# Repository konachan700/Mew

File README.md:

## Mew - hardware password manager

*   [Forum](https://forum.mewhpm.com)
*   [Wiki](https://wiki.mewhpm.com)
*   [Code repo (github)](https://github.com/konachan700/Mew)
*   [Code repo (gitlab mirror)](https://gitlab.com/mewhpm/Mew)
*   [Hardware](https://easyeda.com/konachan.700/MeW_Pro_v2.1)
*	[Android app sources](https://github.com/konachan700/Mew/tree/master/software/MeWSync)

##### • What is it?
It's a small USB device to hold your passwords, private keys and cryptowallets.

*   Easy to use.
*   Fully open sourced.
*   No drivers or propietary software required.
*   Highly protected for critical data.

##### • How does it work?

Connect MeW to a PC or mobile device. Pair MeW with your smartphone via bluetooth. Install the MeW HPM app from Google Play or Appstore. Use it.  

_Demo video will be here a bit later :3_

12 passwords, those you use more often, can be entered directly on the device. Other passwords could be entered by MeW HPM app.  

_Demo video will be here a bit later :3_

You can exchange public keys with your friends directly via bluetooth.

Technically, it is a HID-keyboard.

Passwords are not stored in the device, all passwords are generated on-the-fly depending on the entered PIN-code and internal master key. Nobody and nothing can steal your passwords database, because there is none. If anybody steals the device, he can't bruteforce it - for each PIN-code the device generate different passwords, and, if you set this option, fake logins will be shown.  

Your private keys and wallets, that are stored on the device, are encrypted with AES-256. Encryption key is generated from master key and pin-code on-the-fly. Master key has been stored internally and can't be extracted, of course, if you set the maximum security level.

##### • I lost my MeW. How can I get my passwords back?

When you are starting your MeW for the first time with normal security level, the device key will shown. Save the device key at a secure place. MeW has a cloud backup for encrypted master keys. For recovery of your passwords on a new device you have to enter a device key in the application, and enter you PIN-code in MeW.

In the high security mode cloud backup will disabled, because in this mode the encrypted master key i can't be extracted from the device. If you lose your MeW or forgot a PIN-code, you loose all you passwords.

## • Android application screenshots
&nbsp;&nbsp;&nbsp;&nbsp;&nbsp;&nbsp;&nbsp;&nbsp;&nbsp;&nbsp;&nbsp;&nbsp;

## • Device photos
&nbsp;&nbsp;&nbsp;&nbsp;

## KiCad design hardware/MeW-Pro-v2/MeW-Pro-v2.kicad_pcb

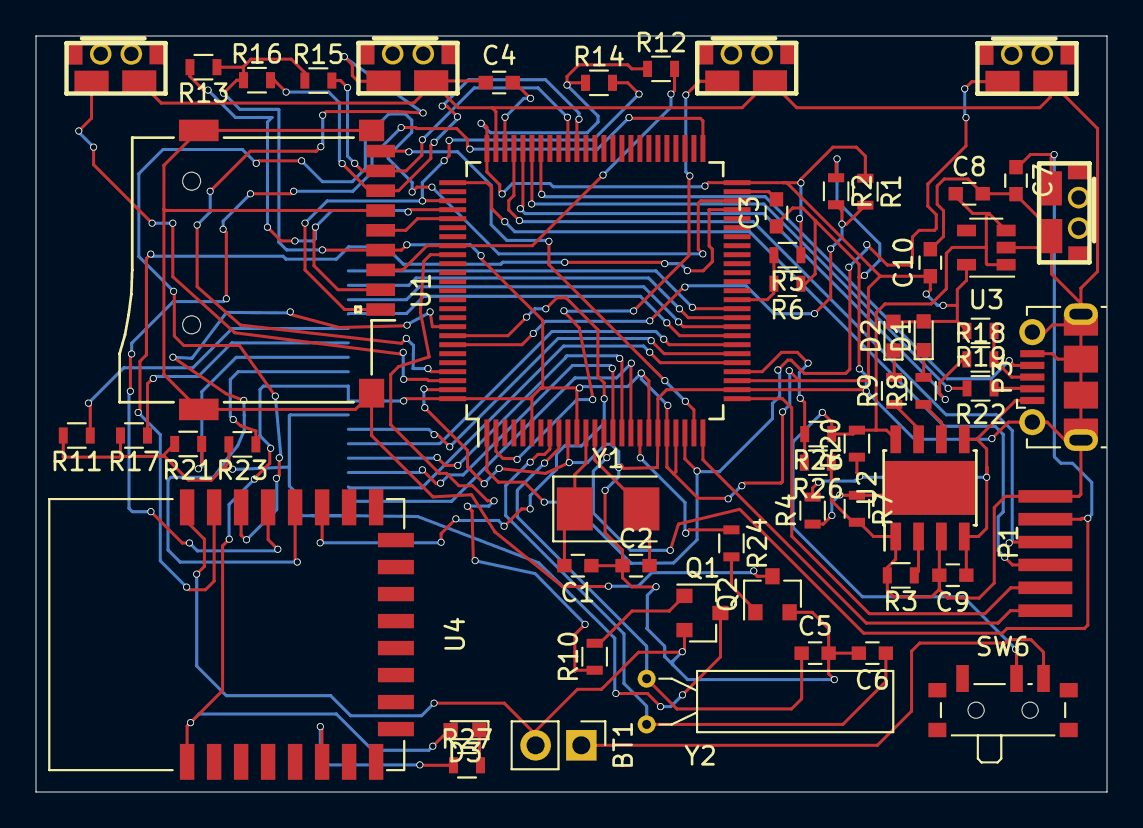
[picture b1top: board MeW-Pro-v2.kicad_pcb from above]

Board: 2 copper layers, 59.5 x 42.0 mm, 59 parts (1 on the bottom side), 68 nets.

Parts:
BT1: Battery; Pin_Header_Straight_1x02_Pitch2.54mm
C1, C2, C5, C6: 22; C_0603
C3, C4: 2.2uF; C_0603
C7: 0.1uF; C_0603
C8, C9, C10: 1uF; C_0603
CON1: uSD_Card; Conn_uSDcard
D1, D2, D3: LED; LED_0603
P1: CONN_01X06; debug_conn_x6
P2: CONN_01X18; DISP1
P3: USB_OTG; USB_Micro-B_Molex-105017-0001
Q1, Q2: 2N7002; SOT-23
R1, R2, R4, R5, R6, R7, R20: 0; R_0603
R3: 10k; R_0603
R8, R9, R19, R27: 1k5; R_0603
R10, R24: 100; R_0603
R11, R17, R21, R23: 63; R_0603
R12, R13, R14, R15, R16: 33k; R_0603
R18, R22: 22R; R_0603
R25, R26: 100k; R_0603
SW1: SW_UP; SMDBTN2
SW2: SW_DOWN; SMDBTN2
SW3: SW_OK; SMDBTN2
SW4: SW_BACK; SMDBTN2
SW5: SW_RESET; SMDBTN2
SW6: SWITCH_INV; SW_SPDT_PCM12
U1: STM32F437VGTx; LQFP-100_14x14mm_Pitch0.5mm
U2: TP4056; SOIC-8_3.9x4.9mm_Pitch1.27mm_9pin
U3: TLV70230DBV; SOT-23-5
U4: JDY-08; JDY-08_HandSoldering
Y1: Crystal; Crystal_SMD_5032-2pin_5.0x3.2mm
Y2: Crystal; Crystal_AT310_d3.0mm_l10.0mm_Horizontal

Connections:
+3V3: C10.1, CON1.4, D1.2, D2.2, D3.2, P2.9, P2.10, R1.1, R5.1, R12.1, R13.1, R14.1, R15.1, R16.1, R19.2, U1.6, U1.11, U1.19, U1.21, U1.22, U1.28, U1.50, U1.75, U1.100, U3.5, U4.1
/5v-usb: C9.1, P3.1, R4.2, R20.1, U2.4, U2.5
/BLE-IO-OFF: U1.51, U4.21
/BLE-PWRC: U1.48, U4.22
/BLE-RESET: U1.47, U4.23
/BLE-RX: U1.92, U4.20
/BLE-TX: U1.93, U4.19
/BMON: C8.1, R20.2, R25.1, SW6.2, U2.8, U3.1, U3.3
/BOOT0: R1.2, R2.2, U1.94
/BOOT1: R5.2, R6.2, U1.37
/CARD_GND: CON1.6, Q2.3
/CARD_PWR: R24.1, U1.18
/DISP_CLK: P2.3, U1.30
/DISP_CS: P2.5, U1.16
/DISP_D/C: P2.4, U1.15
/DISP_MISO: P2.7, U1.31
/DISP_MOSI: P2.6, U1.32
/DISP_PWR: R10.1, U1.84
/DISP_RES: P2.2, U1.17
/LED-B1: R8.1, U2.6
/LED-B2: R9.1, U2.7
/RESET: C7.1, P1.5, SW5.1, U1.14
/SDIO-CD: CON1.9, U1.24
/SDIO-CLK: CON1.5, U1.80
/SDIO-CMD: CON1.3, R12.2, U1.83
/SDIO-D0: CON1.7, R16.2, U1.65
/SDIO-D1: CON1.8, R15.2, U1.66
/SDIO-D2: CON1.1, R14.2, U1.78
/SDIO-D3: CON1.2, R13.2, U1.79
/TOUCH-0: P2.15, U1.33
/TOUCH-1: P2.16, U1.34
/TOUCH-2: P2.17, U1.35
/TOUCH-3: P2.18, U1.36
/USB-DM: R22.2, U1.70
/USB-DP: R18.1, U1.71
/USB-ID: P3.4, U1.69
/WKUP: SW3.1, U1.1, U1.23
/dSWDCLK: P1.3, U1.76
/dSWDIO: P1.4, U1.72
/dUSART-rx: P1.2, U1.26
/dUSART-tx: P1.1, U1.25
GND: BT1.2, C1.1, C2.1, C3.1, C4.1, C5.2, C6.2, C7.2, C8.2, C9.2, C10.2, P1.6, P3.5, P3.6, Q1.2, Q2.2, R2.1, R3.2, R6.1, R7.2, R26.1, SW1.2, SW2.2, SW3.2, SW4.2, SW5.2, U1.10, U1.20, U1.27, U1.74, U1.99, U2.1, U2.3, U3.2, U4.24
unnamed: BT1.1, SW6.3
unnamed: C1.2, U1.12, Y1.1
unnamed: C2.2, U1.13, Y1.2
unnamed: C3.2, U1.49
unnamed: C4.2, U1.73
unnamed: C5.1, U1.9, Y2.2
unnamed: C6.1, U1.8, Y2.1
unnamed: D1.1, R8.2
unnamed: D2.1, R9.2
unnamed: D3.1, R27.2
unnamed: P2.1, P2.8, Q1.3, R11.2, R17.2, R21.2, R23.2
unnamed: P2.11, R23.1
unnamed: P2.12, R21.1
unnamed: P2.13, R17.1
unnamed: P2.14, R11.1
unnamed: P3.2, R22.1
unnamed: P3.3, R18.2, R19.1
unnamed: Q1.1, R10.2
unnamed: Q2.1, R24.2
unnamed: R3.1, U2.2
unnamed: R4.1, R7.1, U2.9
unnamed: R25.2, R26.2, U1.29
unnamed: R27.1, U4.6
unnamed: SW1.1, U1.97
unnamed: SW2.1, U1.98
unnamed: SW4.1, U1.2

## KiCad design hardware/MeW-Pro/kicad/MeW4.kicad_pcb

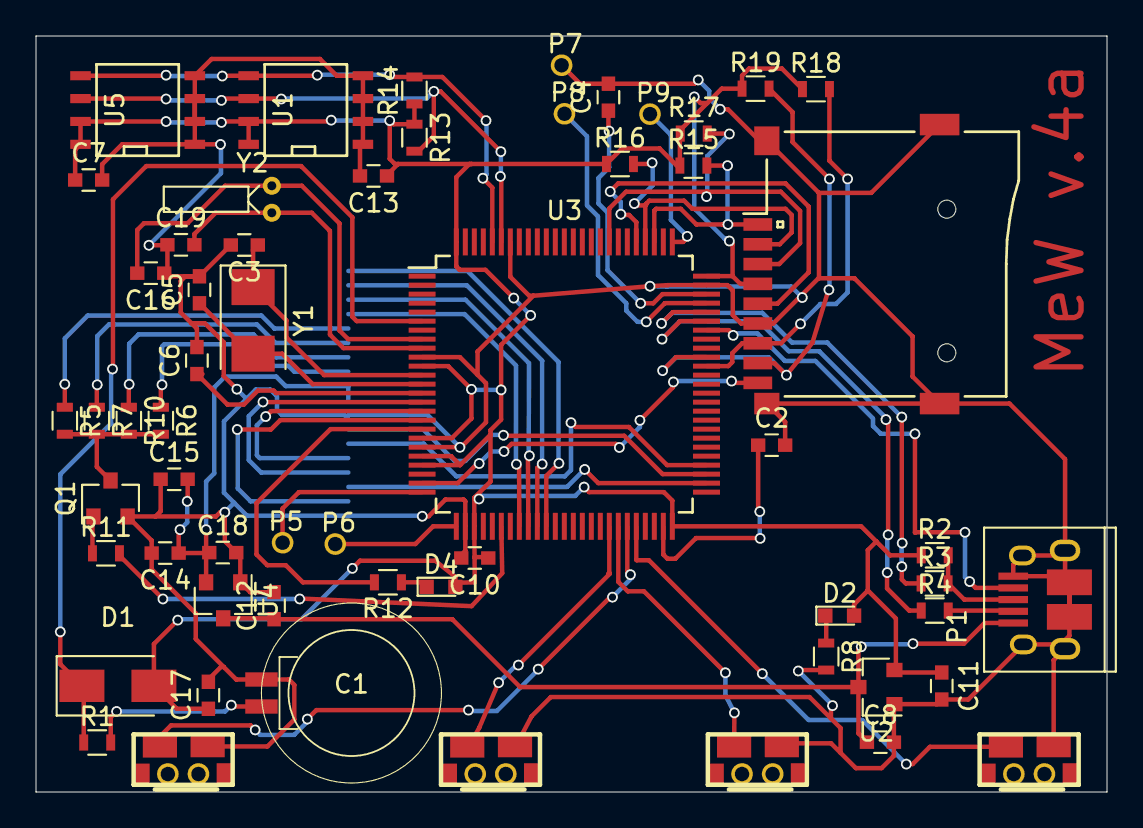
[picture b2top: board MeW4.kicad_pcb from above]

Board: 2 copper layers, 59.5 x 42.0 mm, 59 parts (1 on the bottom side), 55 nets.

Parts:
C1: 0.22F; SCAP-022F
C2, C4: 2.2uF; C_0603
C3, C5, C16, C19: 22; C_0603
C6, C14: 0.1uF; C_0603
C7, C10, C13: 100nF; C_0603
C8, C11, C12, C18: 1uF; C_0603
C15, C17: 0.01uF; C_0603
CON1: uSD_Card; Conn_uSDcard
D1: 1n5819; D_SMA_Standard
D2, D4: LED; LED_0603
P1: USB_OTG; USB_Micro-B_ali1
P4: CONN_01X18; DISP1
P5: TX2; TP_1pin
P6: RX2; TP_1pin
P7: GND; TP_1pin
P8: SWDIO; TP_1pin
P9: SWDCLK; TP_1pin
Q1: 2N7002; SOT-23
R1, R5, R6, R7, R10, R11: 100; R_0603
R2: 1.5k; R_0603
R3, R4: 22; R_0603
R8, R12: 1k; R_0603
R13, R14: 1k5; R_0603
R15, R16, R17, R18, R19: 33k; R_0603
SW1: BACK; SMDBTN2
SW2: ENTER; SMDBTN2
SW3: UP; SMDBTN2
SW4: DOWN; SMDBTN2
U1, U5: 24C16; SOIC-8-N
U2, U4: XC6206P332MR; SOT-23
U3: STM32F217VETx; LQFP-100_14x14mm_Pitch0.5mm
Y1: 8MHz; Crystal_SMD_5032-2pin_5.0x3.2mm
Y2: 32k; Crystal_DS10_d1.0mm_l4.3mm_Horizontal

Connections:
+3V3: C7.1, C10.1, C11.1, C13.1, C17.1, CON1.4, D1.2, D2.2, D4.2, R2.1, R13.1, R14.1, R15.1, R16.1, R17.1, R18.1, R19.1, U1.7, U1.8, U2.2, U3.11, U3.19, U3.21, U3.22, U3.28, U3.50, U3.75, U3.100, U5.7, U5.8
/ADC_1: P4.17, U3.35
/ADC_2: P4.18, U3.36
/B1: SW1.2, U3.43
/B2: SW2.2, U3.44
/B3: SW3.2, U3.45
/B4: SW4.2, U3.46
/CD: CON1.9, U3.24
/DISP_CLK: P4.3, U3.52
/DISP_CS: P4.5, U3.16
/DISP_D/C: P4.4, U3.15
/DISP_MISO: P4.7, U3.53
/DISP_MOSI: P4.6, U3.54
/DISP_PWM: Q1.1, R11.1
/DISP_RES: P4.2, U3.17
/GPIO_X: P4.15, U3.33
/GPIO_Y: P4.16, U3.34
/SDIO_CLK: CON1.5, U3.80
/SDIO_CMD: CON1.3, R17.2, U3.83
/SDIO_D0: CON1.7, R18.2, U3.65
/SDIO_D1: CON1.8, R19.2, U3.66
/SDIO_D2: CON1.1, R15.2, U3.78
/SDIO_D3: CON1.2, R16.2, U3.79
/USB-DM: R4.1, U3.70
/USB-DP: R3.1, U3.71
/USB-ID: P1.4, U3.69
/VBAT_RTC: D1.1, R1.1, U3.6
/i2c_SCL: R13.2, U1.6, U3.95, U5.6
/i2c_SDA: R14.2, U1.5, U3.96, U5.5
GND: C1.2, C2.2, C3.2, C4.2, C5.2, C6.2, C7.2, C8.2, C10.2, C11.2, C12.2, C13.2, C14.2, C15.1, C16.1, C17.2, C18.2, C19.1, CON1.6, P1.5, P1.6, P4.1, P4.8, P7.1, Q1.2, R8.2, SW1.1, SW2.1, SW3.1, SW4.1, U1.1, U1.2, U1.3, U1.4, U2.1, U3.10, U3.20, U3.27, U3.74, U3.94, U4.1, U5.1, U5.2, U5.3, U5.4
unnamed: C1.1, R1.2
unnamed: C2.1, U3.49
unnamed: C3.1, U3.12, Y1.1
unnamed: C4.1, U3.73
unnamed: C5.1, U3.13, Y1.2
unnamed: C6.1, U3.14
unnamed: C8.1, C12.1, P1.1, U2.3, U4.3
unnamed: C14.1, C15.2, C18.1, P4.9, P4.10, U4.2
unnamed: C16.2, U3.8, Y2.1
unnamed: C19.2, U3.9, Y2.2
unnamed: D2.1, R8.1
unnamed: D4.1, R12.1
unnamed: P1.2, R4.2
unnamed: P1.3, R2.2, R3.2
unnamed: P4.11, R6.1
unnamed: P4.12, R10.1
unnamed: P4.13, R7.1
unnamed: P4.14, R5.1
unnamed: P5.1, U3.25
unnamed: P6.1, U3.26
unnamed: P8.1, U3.72
unnamed: P9.1, U3.76
unnamed: Q1.3, R5.2, R6.2, R7.2, R10.2
unnamed: R11.2, U3.31
unnamed: R12.2, U3.18

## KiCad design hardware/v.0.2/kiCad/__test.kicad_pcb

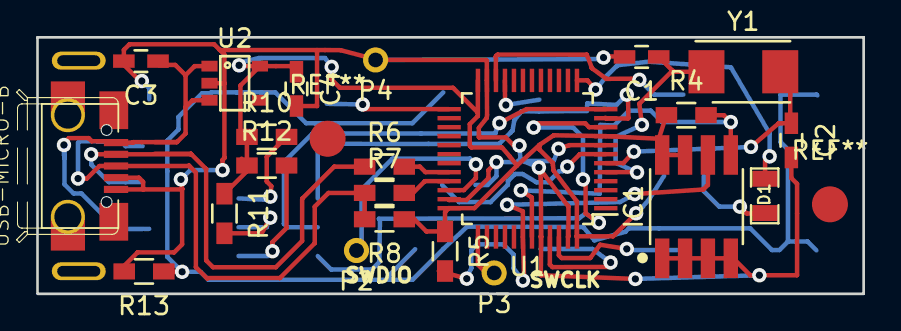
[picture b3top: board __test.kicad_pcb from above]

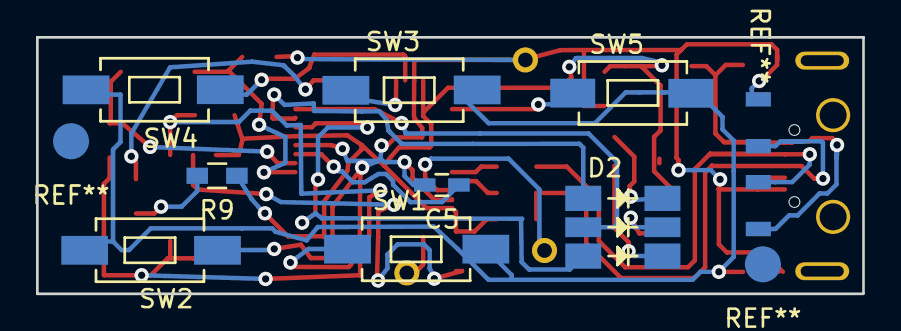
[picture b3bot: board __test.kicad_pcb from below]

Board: 2 copper layers, 45.9 x 14.2 mm, 30 parts (8 on the bottom side), 28 nets.

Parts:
C1, C2: 22; C_0603_HandSoldering
C3: 100nf; C_0603_HandSoldering
C4: 1mf; C_0603_HandSoldering
C5: 0.1mf; C_0603_HandSoldering
CON1: USB-MICRO-B; USB_MICRO_B_SMD
D1: YELLOW; SM0805
D2: LED_RGB_0505; LED_5050_RGB
IC1: ATSHA204A; SO-8_EP1
P2: 1; CONN_2.54mm_1x1
P3: 3; CONN_2.54mm_1x1
P4: 2; CONN_2.54mm_1x1
R4, R5: 1k2; R_0603_HandSoldering
R6, R7: 22; R_0603_HandSoldering
R8, R10, R11, R12: 1k5; R_0603_HandSoldering
R9: 1k; R_0603_HandSoldering
R13: 330; R_0603_HandSoldering
SW1, SW2, SW3, SW4, SW5: SW_PUSH; SW_SPST_EVQPE1
U1: STM32F103C8; LQFP-48_7x7mm_Pitch0.5mm
U2: TLV70033DDC; SOT-23-5
Y1: Crystal; Crystal_SMD_5032_2Pads

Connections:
+3V3: C4.1, IC1.8, R4.1, R5.1, R8.1, R9.1, R10.1, R11.1, R12.1, U1.9, U1.24, U1.36, U1.48, U2.5
/BTN_1: SW1.1, U1.45
/BTN_2: SW2.1, U1.46
/BTN_3: SW3.1, U1.21
/BTN_4: SW4.1, U1.22
/BTN_5: SW5.1, U1.25
/I2C_SCL_1: IC1.6, R5.2, U1.42
/I2C_SDA_1: IC1.5, R4.2, U1.43
/LED_B: D2.3, U1.10
/LED_G: D2.2, U1.12
/LED_R: D2.1, U1.11
/LED_READY: D1.1, U1.13
/SWCLK: P3.1, U1.37
/SWDIO: P2.1, U1.34
/USB_DM: R6.2, U1.32
/USB_DP: R7.2, U1.33
GND: C1.2, C2.2, C3.2, C4.2, C5.2, CON1.4, IC1.4, P4.1, R13.2, U1.8, U1.23, U1.35, U1.44, U1.47, U2.2
unnamed: C1.1, U1.5, Y1.1
unnamed: C2.1, U1.6, Y1.2
unnamed: C3.1, CON1.1, U2.1, U2.3
unnamed: C5.1, U1.7
unnamed: D1.2, R9.2
unnamed: D2.4, R12.2
unnamed: D2.5, R11.2
unnamed: D2.6, R10.2
unnamed: CON1.2, R6.1
unnamed: CON1.3, R7.1, R8.2
unnamed: R13.1, SW1.2, SW2.2, SW3.2, SW4.2, SW5.2

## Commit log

2016-07-14 Inital commit
2016-07-22 Add new firmware for v.0.2
    It's not work yet.
2016-08-03 add firmware v.0.3, based on opencm3
2016-08-04 Убрал баг с платы
    На второй плате обнаружился баг, забыл развести конденсатор на reset и
    замкнуть ноги 4-5 usb-разъема. Заодно сделал универсальным посадочное
    место SO8, теперь туда можно припаять как ATHSA204A, так и 24cXX eeprom.
2016-08-14 Мелкая правка платы
    Поставил чуть другие кнопки, тех не найти.
    Поставил реперы.
2016-09-07 Мелкие правки платы
2016-09-07 scr code update
2017-05-29 Навел порядок в файлах проекта, добавил файлы проекта MeW Pro
2017-05-29 add dma-i2c reading support
2017-05-31 Add i2c dma&isr, remove slowly polling code
2017-06-05 add sdio
2017-06-09 add hardware aes256
2017-06-10 add i2c eeprom support
2017-06-11 add menu
2017-06-12 fix bugs and add usb cdc
2017-06-13 Начал писать софтину для десктопа на жаве, начал пилить протокол для конфигурации через usb cdc.
2017-06-14 Мелкие правки
2017-06-19 add usb msd support\nРазработка пока приостановлена на недельку-другую - купил чипы с али, пришли глючные - отваливается usb. Заказал у офдилера, жду.
2017-06-19 add new hardware
2018-08-28 sync repo with gitlab
2018-10-22 add case and logo.svg
2018-10-22 fix readme mistakes =)
2018-10-27 Fixed typos and grammar
2018-12-13 add packet parser for BLE
2019-03-06 add android app; add photos; add kicad sources for old board;
2019-12-01 Update the firmware
2020-05-18 add bootloader template
2020-05-18 add mew-fw
2020-05-18 fix ep len
2020-05-19 fix firmware update sw
2020-05-19 fix load&verify app
2020-05-20 start changing usb descriptors
2020-05-21 fix usb descriptors for composite device
